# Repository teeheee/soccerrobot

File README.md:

This is a prototype. Use at your own risk.... ;)

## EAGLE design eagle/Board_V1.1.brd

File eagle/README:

Version 1.0 is the current used version. It has major errors which need to be fixed after etching (mirrord components)

Version 1.1 is the corrected version. I didn't have time to fix it so be aware of more errors.

IMPORTANT:

	Dont forget to disconnect the onboard 3,3V Voltage generator of your teensy!

TODO

this board fries a teensy occasionally (3 for 2 Robots over a Year). If you know why please tell me!!! -> alexander.ulbrich@uni-ulm.de

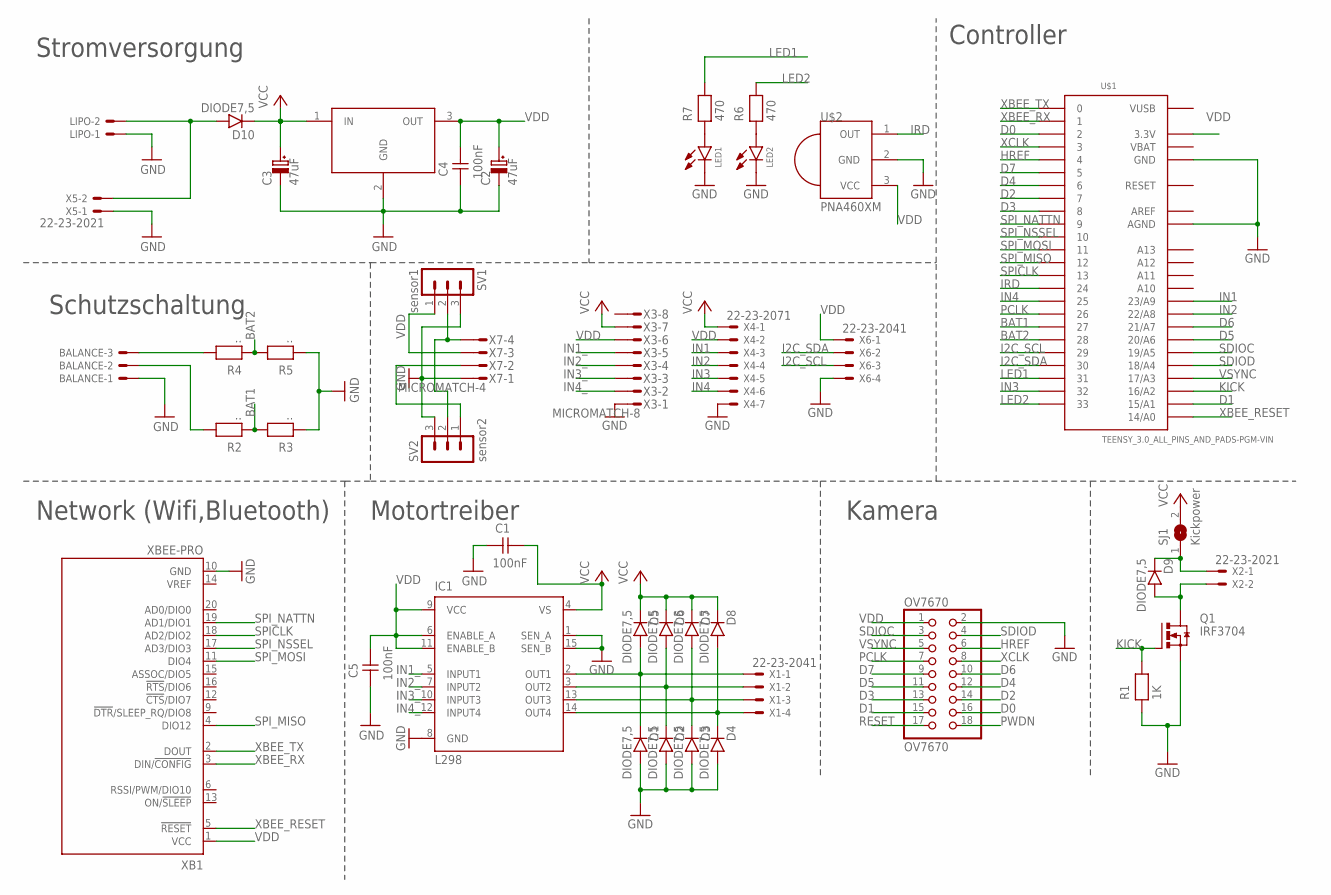
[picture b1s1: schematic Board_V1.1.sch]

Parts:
BALANCE: 22-23-2031
C1, C4, C5: 100nF; 0805
C2, C3: 47uF; C-8.5
D1, D2, D3, D4, D5, D6, D7, D8, D9, D10: DIODE7,5; D-7.5
IC1: L298; MULTIWATT-15
IT1: LM3940IT-3.3; TO220V
LED1: green; LED3MM
LED2: red; LED3MM
LIPO: 22-23-2021
OV7670: OV7670; 2X09
Q1: IRF3704; TO220AH
R1: 1K; 0805
R2, R3, R4, R5: ..; 0805
R6, R7: 470; 0805
SJ1: Kickpower; SJW
SV1: sensor1; MA03-1
SV2: sensor2; MA03-1
U$1: TEENSY_3.0_ALL_PINS_AND_PADS-PGM-VIN; TEENSY_3.0_ALLPINS-PGM-VIN
U$2: PNA460XM
X1, X6: 22-23-2041
X2, X5: 22-23-2021
X3: MICROMATCH-8
X4: 22-23-2071
X7: MICROMATCH-4
XB1: XBEE-PRO

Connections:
AREF: U$1.AREF
BAT1: R2.1, R3.2, U$1.27
BAT2: R4.1, R5.2, U$1.28
D0: OV7670.16, U$1.2
D1: OV7670.15, U$1.15/A1
D2: OV7670.14, U$1.7
D3: OV7670.13, U$1.8
D4: OV7670.12, U$1.6
D5: OV7670.11, U$1.20/A6
D6: OV7670.10, U$1.21/A7
D7: OV7670.9, U$1.5
GND: BALANCE.1, C1.1, C2.P$1, C3.P$1, C4.1, C5.1, D1.A, D2.A, D3.A, D4.A, IC1.1 (SEN_A), IC1.8 (GND), IC1.15 (SEN_B), IT1.2 (GND), LED1.K, LED2.K, LIPO.1, OV7670.2, Q1.E (S), R1.1, R3.1, R5.1, SV1.3, SV2.3, U$1.AGND, U$1.GND, U$1.GND1 (GND), U$1.GND2 (GND), U$2.2 (GND), X3.1, X4.7, X5.1, X6.4, X7.1, XB1.10 (GND)
HREF: OV7670.6, U$1.4
I2C_SCL: U$1.29, X6.3
I2C_SDA: U$1.30, X6.2
IN1: U$1.23/A9, X4.3
IN1_: IC1.5 (INPUT1), X3.5
IN2: U$1.22/A8, X4.4
IN2_: IC1.7 (INPUT2), X3.4
IN3: U$1.32, X4.5
IN3_: IC1.10 (INPUT3), X3.3
IN4: U$1.25, X4.6
IN4_: IC1.12 (INPUT4), X3.2
IRD: U$1.24, U$2.1 (OUT)
KICK: Q1.B (G), R1.2, U$1.16/A2
LED1: R7.2, U$1.31
LED2: R6.2, U$1.33
unnamed: D1.K, D5.A, IC1.2 (OUT1), X1.1
unnamed: D2.K, D6.A, IC1.3 (OUT2), X1.2
unnamed: LED2.A, R6.1
unnamed: BALANCE.2, R2.2
unnamed: D3.K, D7.A, IC1.13 (OUT3), X1.3
unnamed: D4.K, D8.A, IC1.14 (OUT4), X1.4
unnamed: BALANCE.3, R4.2
unnamed: LED1.A, R7.1
unnamed: SV2.1, X7.2
unnamed: SV1.1, X7.3
P1: D9.A, Q1.C (D), X2.2
P2: D9.K, SJ1.1, X2.1
P3: D10.A, LIPO.2, X5.2
PCLK: OV7670.7, U$1.26
PWDN: OV7670.18
RESET: OV7670.17
SDIOC: OV7670.3, U$1.19/A5
SDIOD: OV7670.4, U$1.18/A4
SPICLK: U$1.13, XB1.18 (AD2/DIO2)
SPI_MISO: U$1.12, XB1.4 (DIO12)
SPI_MOSI: U$1.11, XB1.11 (DIO4)
SPI_NATTN: U$1.9, XB1.19 (AD1/DIO1)
SPI_NSSEL: U$1.10, XB1.17 (AD3/DIO3)
VBAT: U$1.VBAT
VCC: C1.2, C3.P$2, D5.K, D6.K, D7.K, D8.K, D10.K, IC1.4 (VS), IT1.1 (IN), SJ1.2, X3.7, X4.1
VDD: C2.P$2, C4.2, C5.2, IC1.6 (ENABLE_A), IC1.9 (VCC), IC1.11 (ENABLE_B), IT1.3 (OUT), OV7670.1, SV1.2, SV2.2, U$1.3.3V, U$1.3.3V1 (3.3V), U$1.3.3V2 (3.3V), U$2.3 (VCC), X3.6, X4.2, X6.1, X7.4, XB1.1 (VCC)
VSYNC: OV7670.5, U$1.17/A3
VUSB: U$1.VUSB
XBEE_RESET: U$1.14/A0, XB1.5 (!RESET)
XBEE_RX: U$1.1, XB1.3 (DIN/!CONFIG)
XBEE_TX: U$1.0, XB1.2 (DOUT)
XCLK: OV7670.8, U$1.3

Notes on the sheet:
Network (Wifi,Bluetooth)
Motortreiber
Kamera
Controller
Stromversorgung
Schutzschaltung

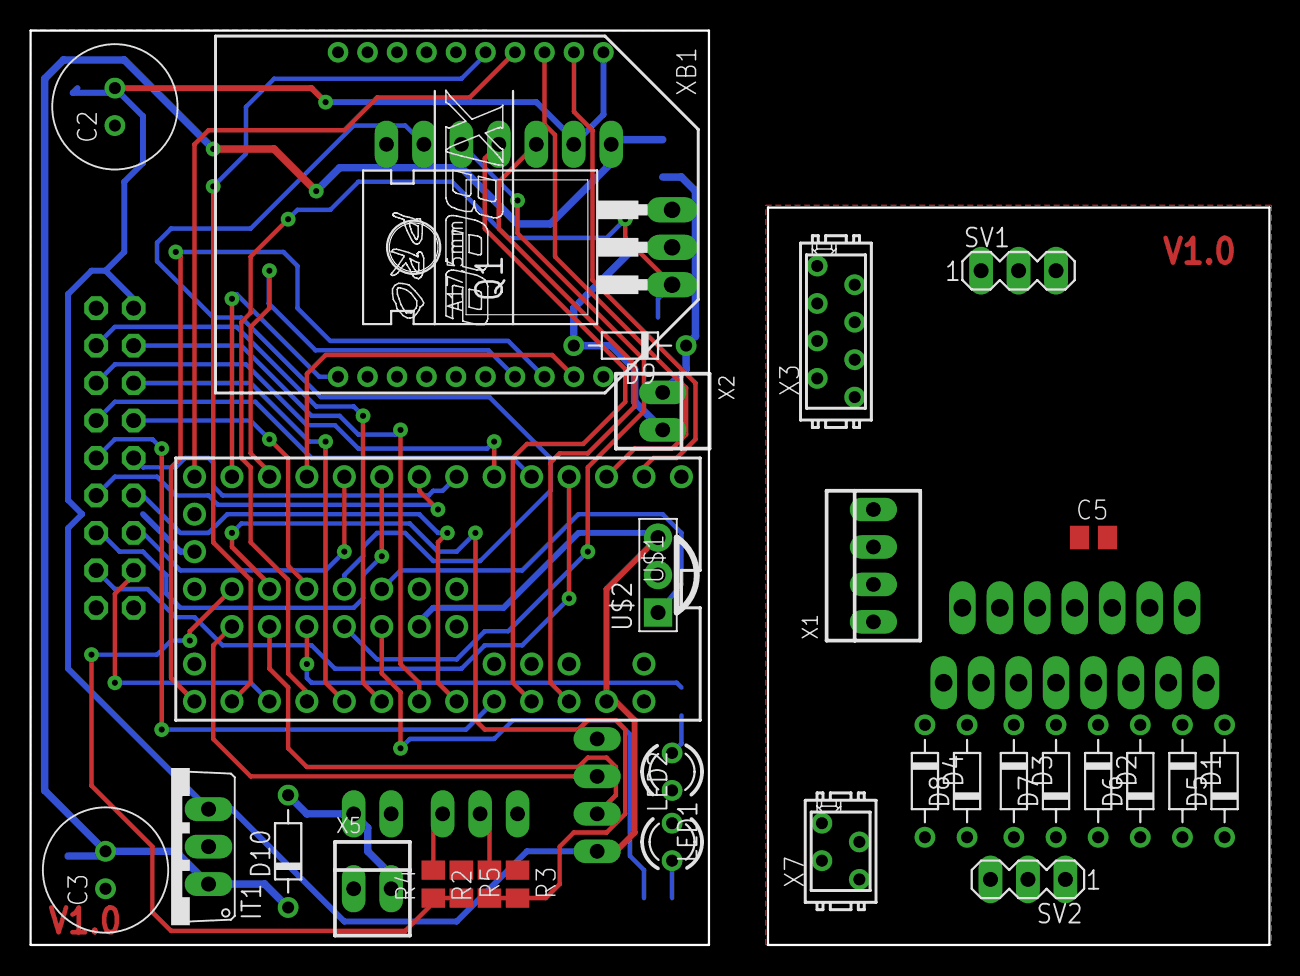
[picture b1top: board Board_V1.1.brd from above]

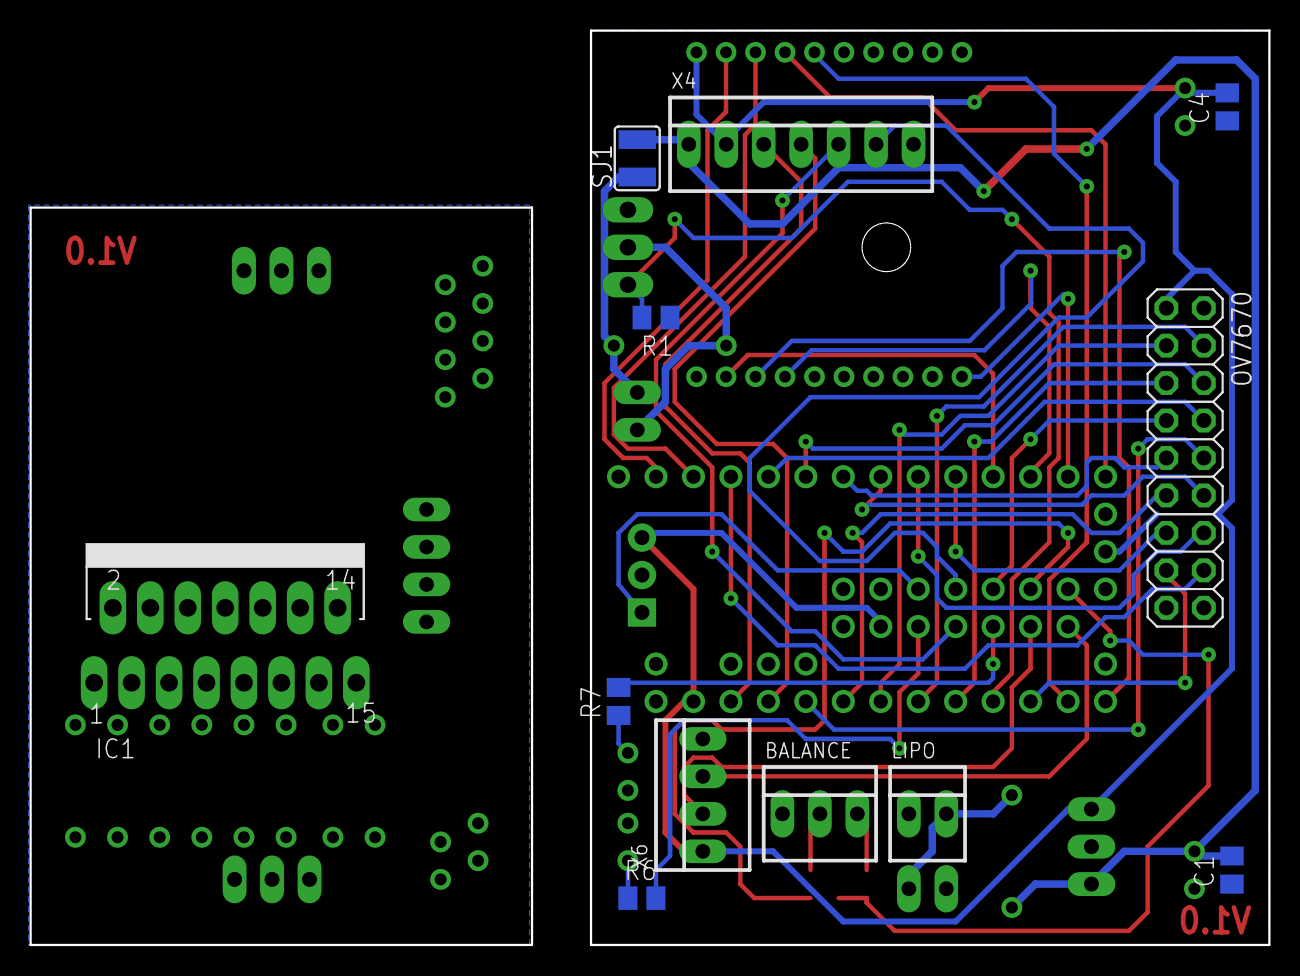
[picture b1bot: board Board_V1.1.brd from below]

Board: 2 copper layers, 84.0 x 62.0 mm, 43 parts (12 on the bottom side), 54 nets.

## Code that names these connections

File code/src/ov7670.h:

#ifndef _OV7670_
#define _OV7670_

#include "Arduino.h"
#include "sccb.h"


// image format QCIF,QVGA,CIF,VGA (VGA is still not working)
#define CIF

#ifdef QCIF

#define LINEBUFFERSIZE 20
#define WIDTH 174*2
#define HEIGHT 144
#endif
#ifdef QVGA

#define LINEBUFFERSIZE 16
#define WIDTH 320*2
#define HEIGHT 240
#endif
#ifdef CIF //352x288

#define LINEBUFFERSIZE 8
#define WIDTH (352)*2
#define HEIGHT 288
#endif
#ifdef VGA //352x288
#define LINEBUFFERSIZE 4
#define WIDTH 640*2
#define HEIGHT 480
#endif

//the size of one raw image
#define BUFFERSIZE LINEBUFFERSIZE*WIDTH
//the size of one line of a raw image
#define DMA_DATALENGTH WIDTH


#define DO_PIN 2
#define D1_PIN 14
#define D2_PIN 7
#define D3_PIN 8
#define D4_PIN 6
#define D5_PIN 20
#define D6_PIN 21
#define D7_PIN 5
#define HREF_PIN 4 //(PTA13)
#define VSYNC_PIN 17 //(PTC2)
#define XCLK_PIN 3
#define PCLK_PIN 26


//initalise the camera
void init_ov7670();

//returns a pointer to the line index
uint8_t* getline(int index);

// free line to save ram and to get a new line
void freeline(int index);

//stop and start driver if something went wrong
void startimageandfreeram();
void stopimageandfreeram();

//some debug functions...
void dummyprocessor();
void printdebug();
double getfps();

//change configuration of ov7670 registers over sccb
int changeregister(uint8_t adress,uint8_t data);

#endif

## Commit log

2016-03-03 Delete wifi.h~
    deleted some unnecessary files
2016-03-03 Delete soccerrobot.cpp~
    delet some unnecessary files
2016-03-03 Delete ov7670.h~
    delet some unnecessary files
2016-03-03 Delete ov7670.cpp~
    delet some unnecessary files
2016-03-03 Delete config.h~
    delet some unnecessary files
